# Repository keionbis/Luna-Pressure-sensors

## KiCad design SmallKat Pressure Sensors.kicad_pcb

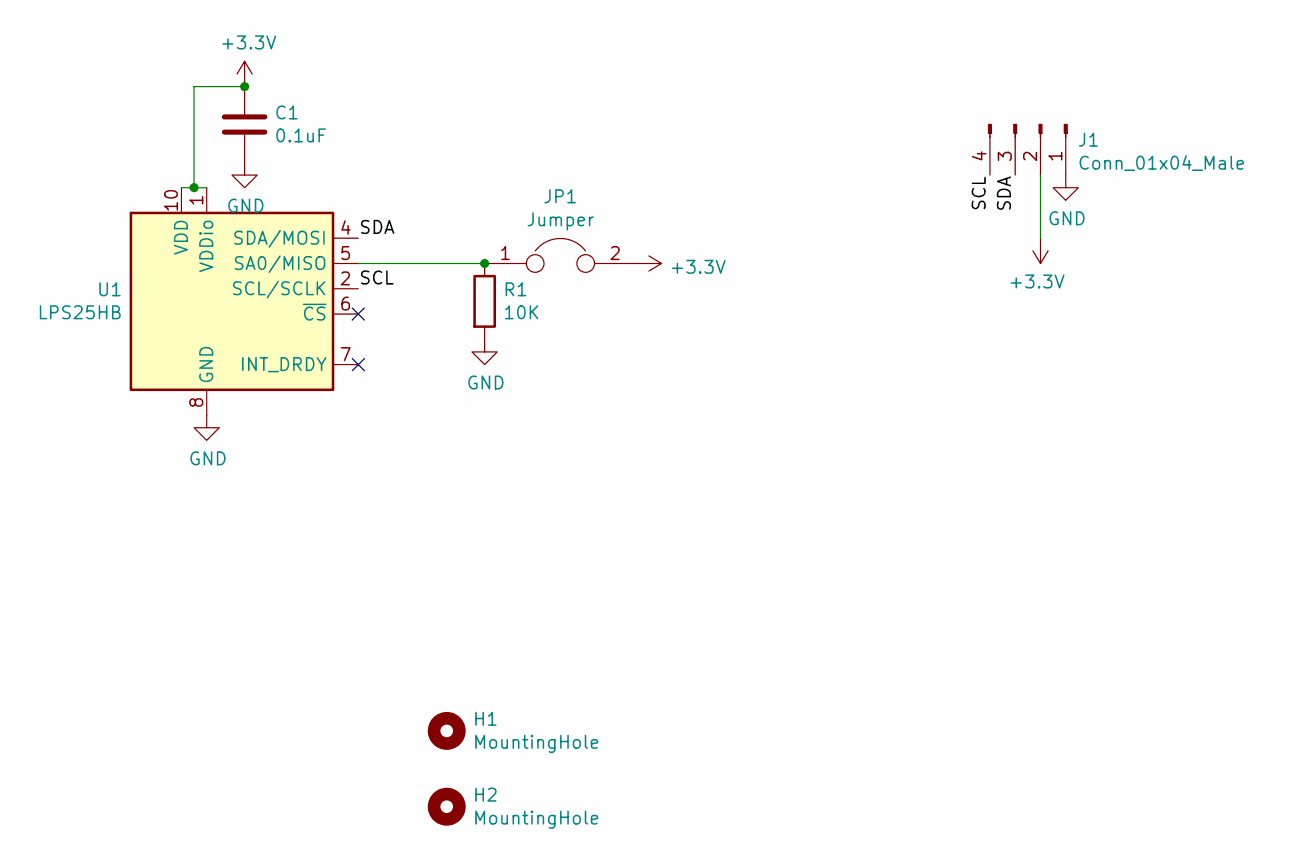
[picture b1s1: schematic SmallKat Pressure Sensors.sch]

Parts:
C1: 0.1uF; C_0402_1005Metric
H1, H2: MountingHole; MountingHole_2.7mm_M2.5
J1: Conn_01x04_Male; JST_SH_SM04B-SRSS-TB_1x04-1MP_P1.00mm_Horizontal
JP1: Jumper; SolderJumper-2_P1.3mm_Bridged_Pad1.0x1.5mm
R1: 10K; R_0402_1005Metric
U1: LPS25HB; ST_HLGA-10_2.5x2.5mm_P0.6mm_LayoutBorder3x2y

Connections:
+3V3: C1.1, J1.2, JP1.2, U1.1 (VDDio), U1.10 (VDD)
/SCL: J1.4, U1.2 (SCL/SCLK)
/SDA: J1.3, U1.4 (SDA/MOSI)
GND: C1.2, J1.1, R1.2, U1.3 (GND), U1.8 (GND), U1.9 (GND)
unnamed: JP1.1, R1.1, U1.5 (SA0/MISO)

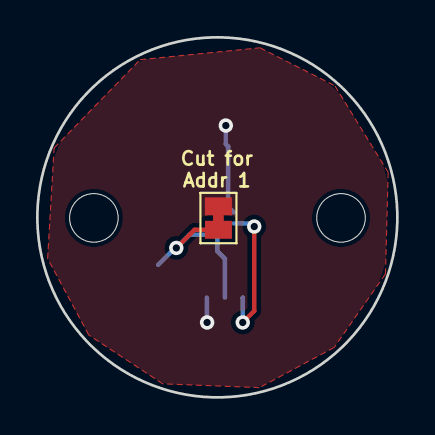
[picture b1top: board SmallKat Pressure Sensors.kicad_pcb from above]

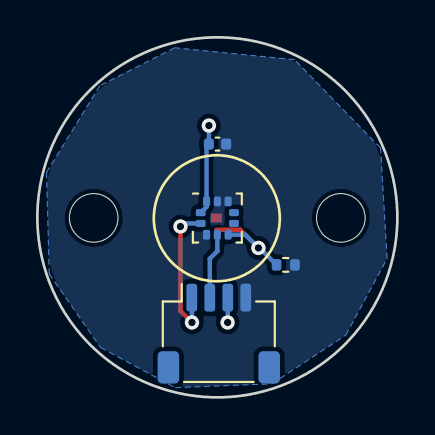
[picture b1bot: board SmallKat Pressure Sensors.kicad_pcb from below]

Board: 2 copper layers, 20.0 x 20.0 mm, 7 parts (4 on the bottom side), 5 nets.

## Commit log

2021-02-03 updated to single sided assembly
